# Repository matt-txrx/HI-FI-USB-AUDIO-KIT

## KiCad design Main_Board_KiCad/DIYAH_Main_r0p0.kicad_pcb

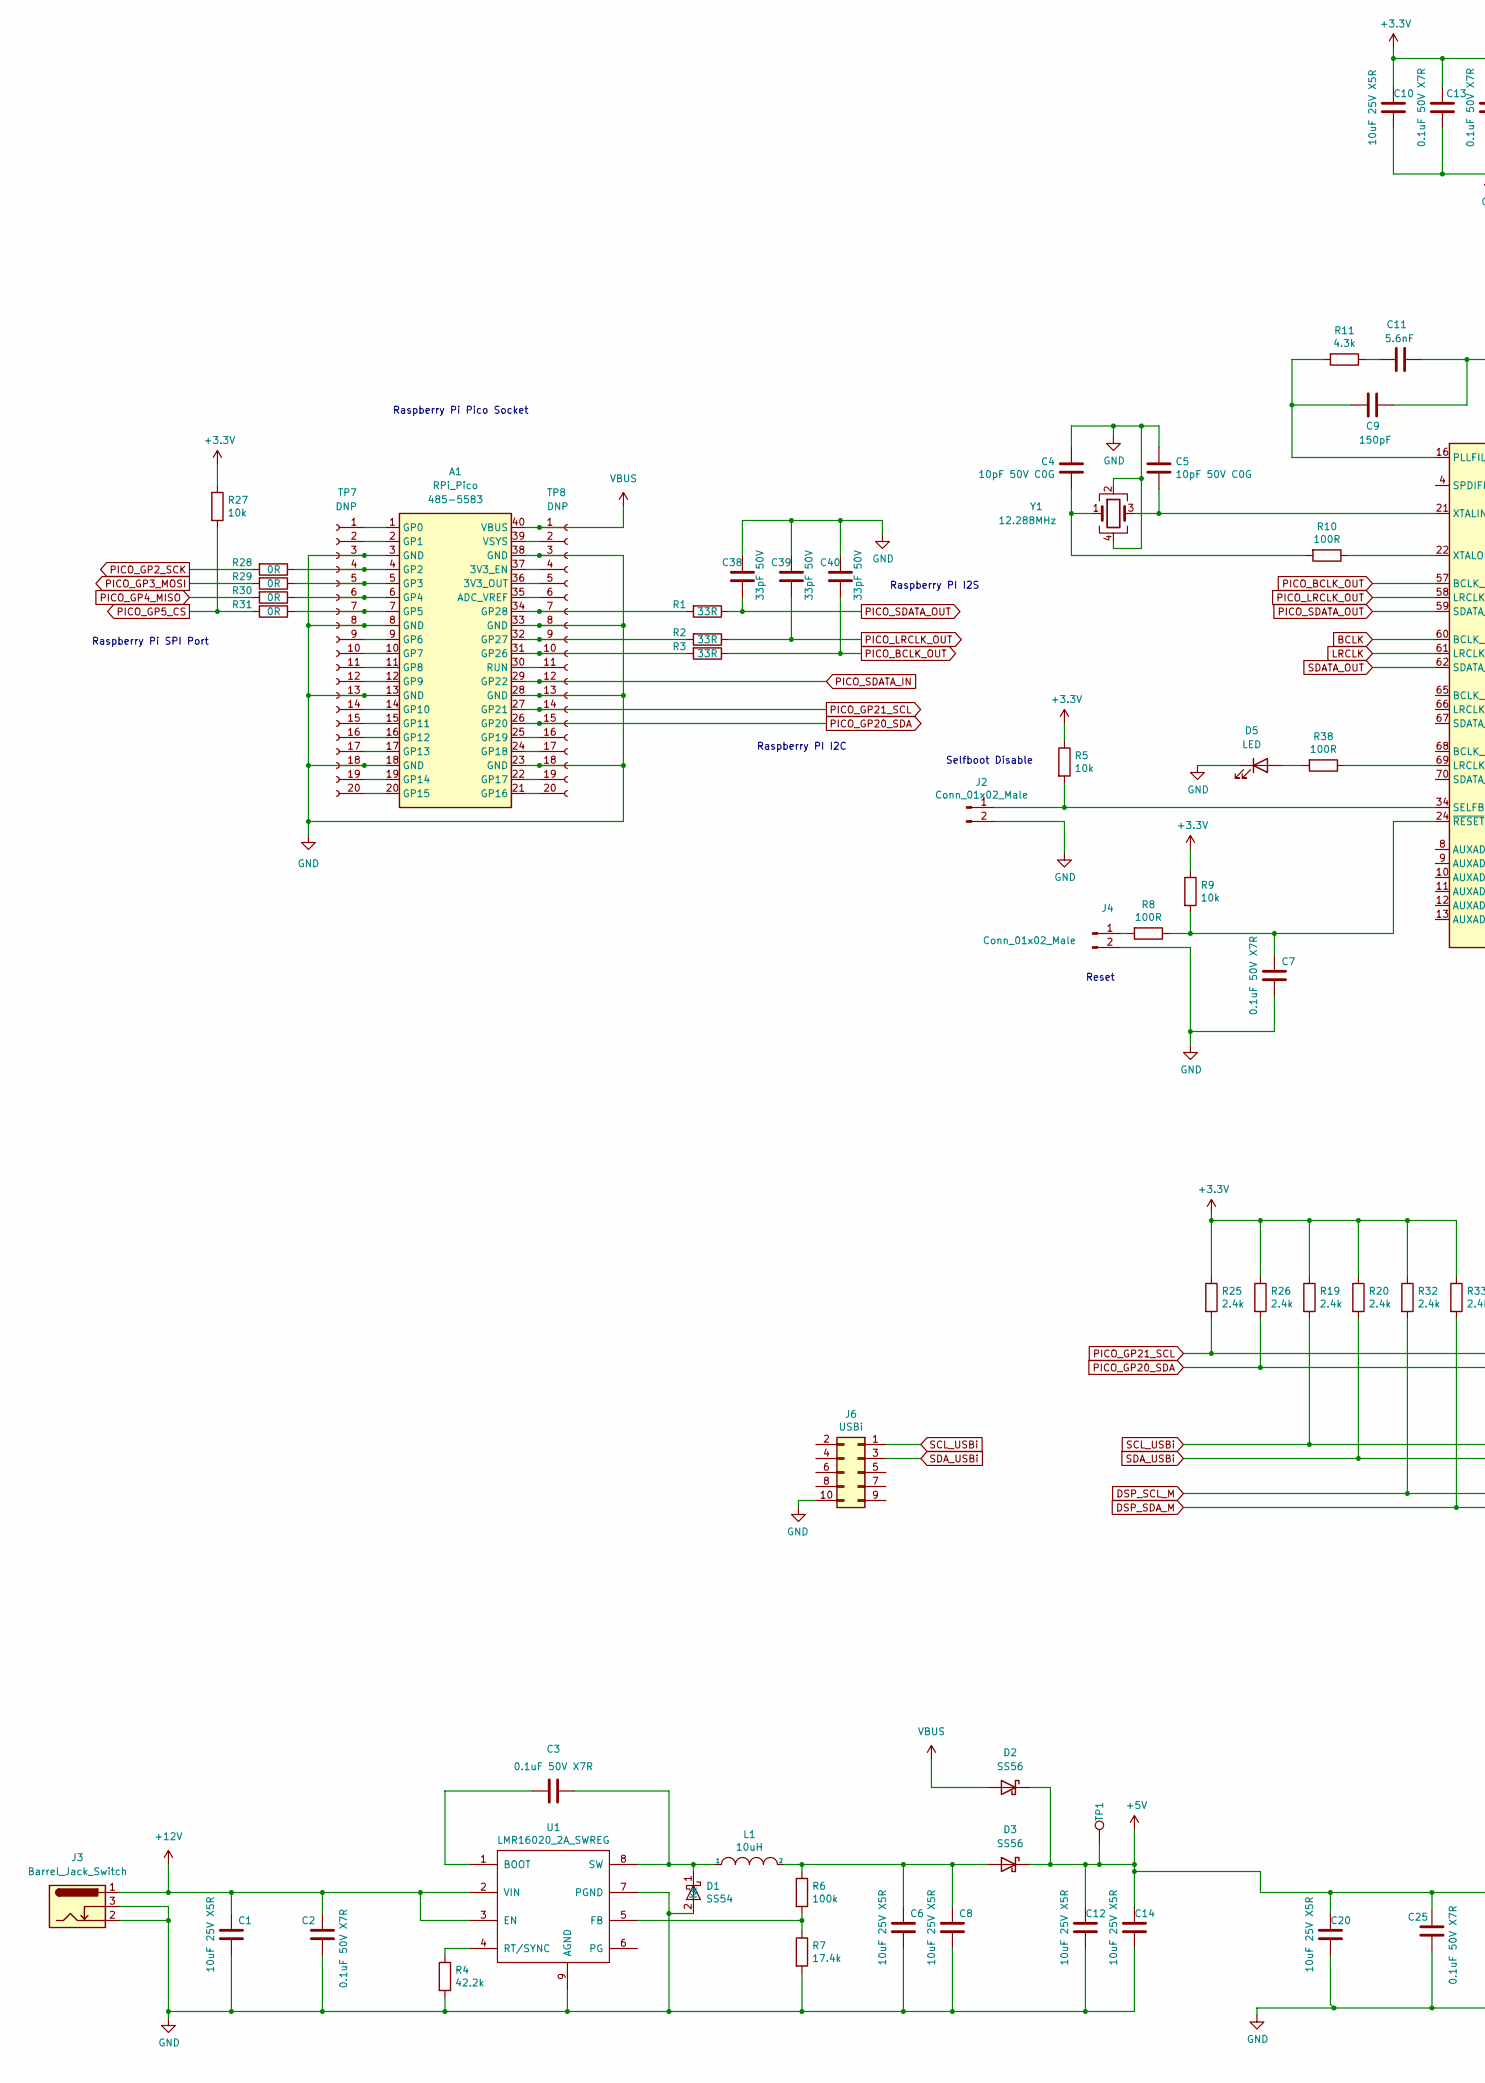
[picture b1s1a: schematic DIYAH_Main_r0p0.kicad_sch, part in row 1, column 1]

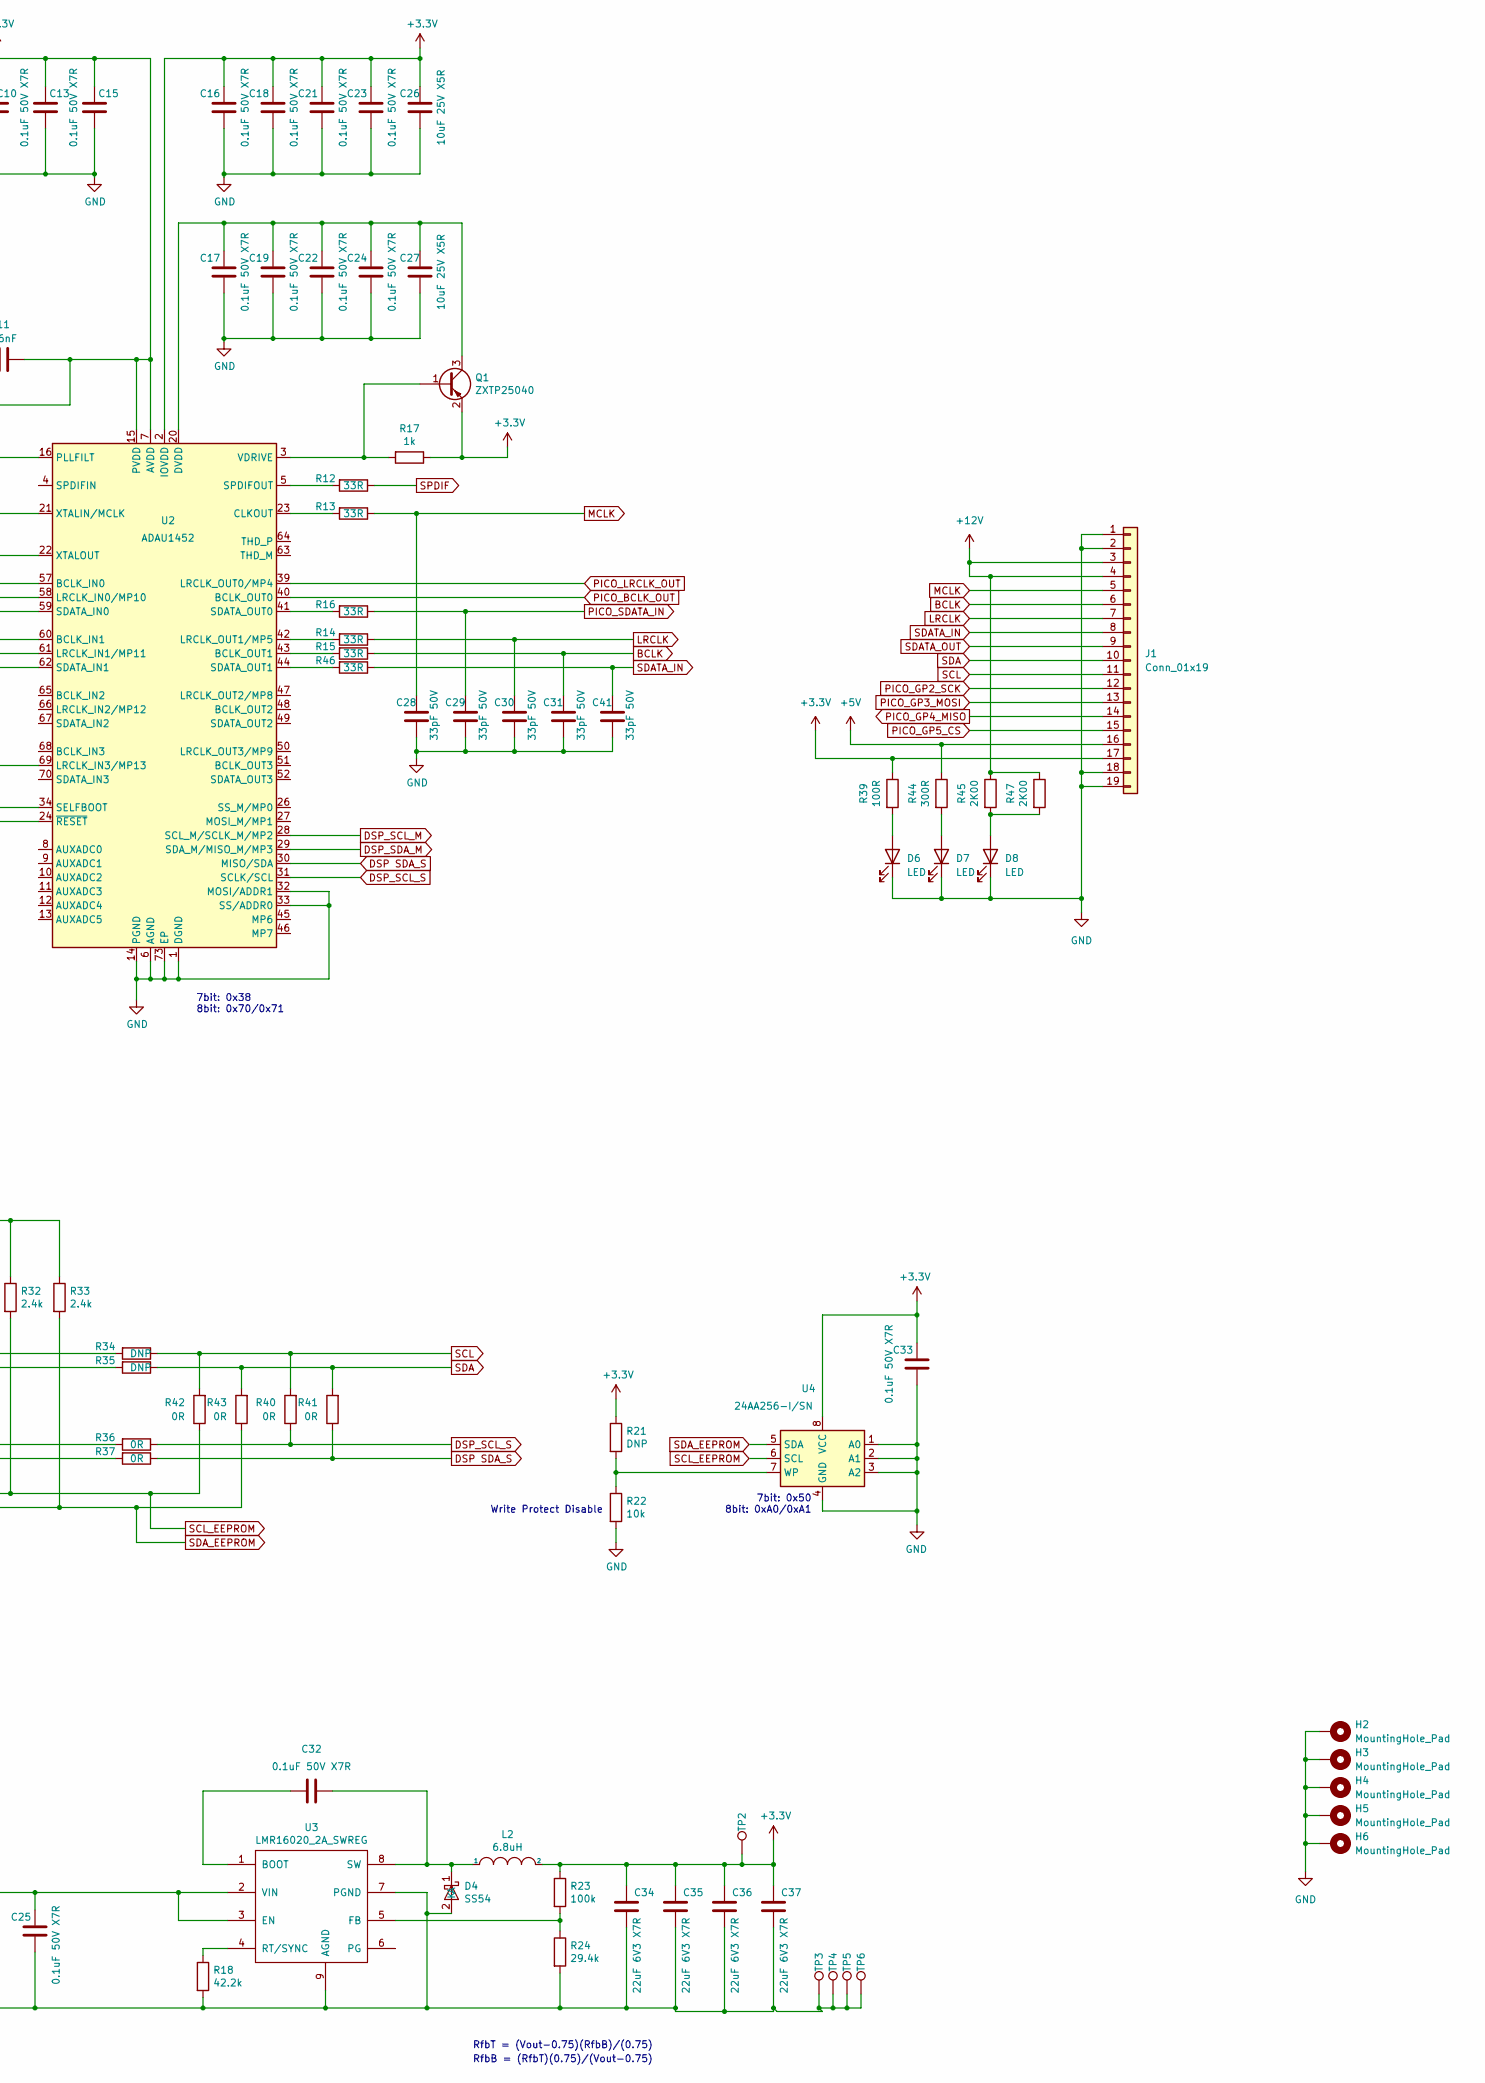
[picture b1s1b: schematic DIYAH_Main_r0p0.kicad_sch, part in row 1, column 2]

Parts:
A1: RPi_Pico; Rpi_Pico; Mouser 485-5583
C1, C6, C8, C10, C12, C14, C20, C26, C27: 10uF 25V X5R; C_0805_2012Metric_Pad1.18x1.45mm_HandSolder; Part Number CL21A106KAYNNNE; LCSC Part # C15850
C2, C3, C7, C13, C15, C16, C17, C18, C19, C21, C22, C23, C24, C25, C32, C33: 0.1uF 50V X7R; C_0603_1608Metric_Pad1.08x0.95mm_HandSolder; Part Number CC0603KRX7R9BB104; LCSC Part # C14663
C4, C5: 10pF 50V C0G; C_0603_1608Metric_Pad1.08x0.95mm_HandSolder; Part Number CL10C100JB8NNNC; LCSC Part # C1634
C9: 150pF; C_0603_1608Metric_Pad1.08x0.95mm_HandSolder; Part Number CL10B151KB8NNNC; LCSC Part # C170148
C11: 5.6nF; C_0603_1608Metric_Pad1.08x0.95mm_HandSolder; Part Number CL10B562KB8NNNC; LCSC Part # C170143
C28, C29, C30, C31, C38, C39, C40, C41: 33pF 50V; C_0603_1608Metric_Pad1.08x0.95mm_HandSolder; Part Number CL10C330JB8NNNC; LCSC Part # C1663
C34, C35, C36, C37: 22uF 6V3 X7R; C_0805_2012Metric_Pad1.18x1.45mm_HandSolder; Part Number CL21A226MAQNNNE; LCSC Part # C45783
D1, D4: SS54; D_SMA; Part Number SS54-HF; Mouser 750-SS54-HF
D2, D3: SS56; D_SMB; LCSC Part # C2897835
D5, D6, D7, D8: LED; LED_1206_3216Metric_Pad1.42x1.75mm_HandSolder; LCSC Part # C434442
H2, H3, H4, H5, H6: MountingHole_Pad; MountingHole_3.2mm_M3_Pad_Via
J1: Conn_01x19; PinSocket_1x19_P2.54mm_Vertical
J2, J4: Conn_01x02_Male; PinHeader_1x02_P2.54mm_Vertical
J3: Barrel_Jack_Switch; BarrelJack_GCT_DCJ200-10-A_Horizontal; Mouser 640-DCJ200-10-A-K1-K
J6: USBi; IDC-Header_2x05_P2.54mm_Vertical
L1: 10uH; Coilcraft_XAL40xx; Part Number XAL4040-103MEC; Mouser 994-XAL4040-103MEC
L2: 6.8uH; L_7.3x7.3_H3.5; Part Number 0618CDMCCDS-6R8MC; Mouser 851-0618CDMCCDS6R8MC
Q1: ZXTP25040; SOT-23; Part Number ZXTP25040DFHTA; Mouser 621-ZXTP25040DFHTA
R1, R2, R3, R12, R13, R14, R15, R16, R46: 33R; R_0603_1608Metric_Pad0.98x0.95mm_HandSolder; Part Number 0603WAF330JT5E; LCSC Part # C23140
R4, R18: 42.2k; R_0603_1608Metric_Pad0.98x0.95mm_HandSolder; Part Number 0603WAF4422T5E; LCSC Part # C23056
R5, R9, R22, R27: 10k; R_0603_1608Metric_Pad0.98x0.95mm_HandSolder; Part Number 0603WAF1002T5E; LCSC Part # C25804
R6, R23: 100k; R_0603_1608Metric_Pad0.98x0.95mm_HandSolder; Part Number 0603WAF1003T5E; LCSC Part # C25803
R7: 17.4k; R_0603_1608Metric_Pad0.98x0.95mm_HandSolder; Part Number 0603WAF1742T5E; LCSC Part # C22819
R8, R10, R38, R39: 100R; R_0603_1608Metric_Pad0.98x0.95mm_HandSolder; Part Number 0603WAF1000T5E; LCSC Part # C22775
R11: 4.3k; R_0603_1608Metric_Pad0.98x0.95mm_HandSolder; Part Number 0603WAF4301T5E; LCSC Part # C23159
R17: 1k; R_0603_1608Metric_Pad0.98x0.95mm_HandSolder; Part Number 0603WAF1001T5E; LCSC Part # C25804
R19, R20, R25, R26, R32, R33: 2.4k; R_0603_1608Metric_Pad0.98x0.95mm_HandSolder; Part Number 0603WAF2401T5E; LCSC Part # C22940
R21, R34, R35: DNP; R_0603_1608Metric_Pad0.98x0.95mm_HandSolder
R24: 29.4k; R_0603_1608Metric_Pad0.98x0.95mm_HandSolder; Part Number 0603WAF2942T5E; LCSC Part # C22974
R28, R29, R30, R31, R36, R37, R40, R41, R42, R43: 0R; R_0603_1608Metric_Pad0.98x0.95mm_HandSolder; Part Number 0603WAF0000T5E; LCSC Part # C21189
R44: 300R; R_0603_1608Metric_Pad0.98x0.95mm_HandSolder; Part Number 0603WAF3000T5E; LCSC Part # C23025
R45, R47: 2K00; R_0603_1608Metric_Pad0.98x0.95mm_HandSolder; Part Number 0603WAF2001T5E; LCSC Part # C22975
TP1, TP2, TP3, TP4, TP5, TP6: DNP; TestPoint_Keystone_5000-5004_Miniature
TP7, TP8: DNP; PinHeader_1x20_P2.54mm_Vertical
U1, U3: LMR16020_2A_SWREG; HSOP-8-1EP_3.9x4.9mm_P1.27mm_EP2.41x3.1mm_ThermalVias; Part Number LMR16020PDDAR; LCSC Part # C190006
U2: ADAU1452; LFCSP-72-1EP_10x10mm_P0.5mm_EP5.3x5.3mm; Part Number ADAU1452WBCPZ; LCSC Part # C403699
U4: 24AA256-I/SN; SOIC-8_3.9x4.9mm_P1.27mm; Part Number 24AA256-I/SN; LCSC Part # C152169
Y1: 12.288MHz; Crystal_SMD_3225-4Pin_3.2x2.5mm_HandSoldering; Part Number SMD-3225_4P 12.288MHZ 12PF 10PPM -40~+8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; LCSC Part # C362472

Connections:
+3.3V: C9.1, C10.1, C11.2, C13.2, C15.2, C16.2, C18.2, C21.2, C23.2, C26.1, C33.2, C34.1, C35.1, C36.1, C37.1, J1.17, L2.2, Q1.2 (E), R5.1, R9.1, R17.1, R19.1, R20.1, R21.1, R23.1, R25.1, R26.1, R27.1, R32.1, R33.1, R39.1, TP2.1, U2.2 (IOVDD), U2.7 (AVDD), U2.15 (PVDD), U2.18 (IOVDD), U2.38 (IOVDD), U2.56 (IOVDD), U4.8 (VCC)
+5V: C12.1, C14.1, C20.1, C25.2, D2.1 (K), D3.1 (K), J1.16, R44.1, TP1.1, U3.2 (VIN), U3.3 (EN)
+12V: C1.1, C2.2, J1.3, J1.4, J3.1, R45.1, R47.1, U1.2 (VIN), U1.3 (EN)
BCLK: C31.1, J1.6, R15.1, U2.60 (BCLK_IN1)
DSP SDA_S: R37.1, R41.1, U2.30 (MISO/SDA)
DSP_SCL_M: R32.2, R42.1, U2.28 (SCL_M/SCLK_M/MP2), U4.6 (SCL)
DSP_SCL_S: R36.1, R40.1, U2.31 (SCLK/SCL)
DSP_SDA_M: R33.2, R43.1, U2.29 (SDA_M/MISO_M/MP3), U4.5 (SDA)
GND: A1.3 (GND), A1.8 (GND), A1.13 (GND), A1.18 (GND), A1.23 (GND), A1.28 (GND), A1.33 (GND), A1.38 (GND), C1.2, C2.1, C4.1, C5.1, C6.2, C7.1, C8.2, C10.2, C12.2, C13.1, C14.2, C15.1, C16.1, C17.1, C18.1, C19.1, C20.2, C21.1, C22.1, C23.1, C24.1, C25.1, C26.2, C27.2, C28.2, C29.2, C30.2, C31.2, C33.1, C34.2, C35.2, C36.2, C37.2, C38.1, C39.1, C40.1, C41.2, D1.2 (A), D4.2 (A), D5.1 (K), D6.1 (K), D7.1 (K), D8.1 (K), H2.1, H3.1, H4.1, H5.1, H6.1, J1.1, J1.2, J1.18, J1.19, J2.2, J3.2, J3.3, J4.2, J6.10, R4.2, R7.2, R18.2, R22.2, R24.2, TP3.1, TP4.1, TP5.1, TP6.1, TP7.3, TP7.8, TP7.13, TP7.18, TP8.3, TP8.8, TP8.13, TP8.18, U1.7 (PGND), U1.9 (AGND), U2.1 (DGND), U2.6 (AGND), U2.14 (PGND), U2.17 (DGND), U2.19 (DGND), U2.25 (DGND), U2.32 (MOSI/ADDR1), U2.33 (SS/ADDR0), U2.36 (DGND), U2.37 (DGND), U2.54 (DGND), U2.55 (DGND), U2.72 (DGND), U2.73 (EP), U3.7 (PGND), U3.9 (AGND), U4.1 (A0), U4.2 (A1), U4.3 (A2), U4.4 (GND), Y1.2, Y1.4
LRCLK: C30.1, J1.7, R14.1, U2.61 (LRCLK_IN1/MP11)
MCLK: C28.1, J1.5, R13.1
unnamed: A1.1 (GP0), TP7.1
unnamed: A1.2 (GP1), TP7.2
unnamed: A1.4 (GP2), R28.1, TP7.4
unnamed: A1.5 (GP3), R29.1, TP7.5
unnamed: A1.6 (GP4), R30.1, TP7.6
unnamed: A1.7 (GP5), R31.1, TP7.7
unnamed: A1.9 (GP6), TP7.9
unnamed: A1.10 (GP7), TP7.10
unnamed: A1.11 (GP8), TP7.11
unnamed: A1.12 (GP9), TP7.12
unnamed: A1.14 (GP10), TP7.14
unnamed: A1.15 (GP11), TP7.15
unnamed: A1.16 (GP12), TP7.16
unnamed: A1.17 (GP13), TP7.17
unnamed: A1.19 (GP14), TP7.19
unnamed: A1.20 (GP15), TP7.20
unnamed: A1.21 (GP16), TP8.20
unnamed: A1.22 (GP17), TP8.19
unnamed: A1.24 (GP18), TP8.17
unnamed: A1.25 (GP19), TP8.16
unnamed: A1.30 (RUN), TP8.11
unnamed: A1.31 (GP26), R3.2, TP8.10
unnamed: A1.32 (GP27), R2.2, TP8.9
unnamed: A1.34 (GP28), R1.2, TP8.7
unnamed: A1.35 (ADC_VREF), TP8.6
unnamed: A1.36 (3V3_OUT), TP8.5
unnamed: A1.37 (3V3_EN), TP8.4
unnamed: A1.39 (VSYS), TP8.2
unnamed: C3.1, D1.1 (K), L1.1, U1.8 (SW)
unnamed: C3.2, U1.1 (BOOT)
unnamed: C4.2, R10.2, Y1.1
unnamed: C5.2, U2.21 (XTALIN/MCLK), Y1.3
unnamed: C6.1, C8.1, D3.2 (A), L1.2, R6.1
unnamed: C7.2, R8.1, R9.2, U2.24 (~RESET)
unnamed: C9.2, R11.2, U2.16 (PLLFILT)
unnamed: C11.1, R11.1
unnamed: C17.2, C19.2, C22.2, C24.2, C27.1, Q1.3 (C), U2.20 (DVDD), U2.35 (DVDD), U2.53 (DVDD), U2.71 (DVDD)
unnamed: C32.1, D4.1 (K), L2.1, U3.8 (SW)
unnamed: C32.2, U3.1 (BOOT)
unnamed: D5.2 (A), R38.2
unnamed: D6.2 (A), R39.2
unnamed: D7.2 (A), R44.2
unnamed: D8.2 (A), R45.2, R47.2
unnamed: J2.1, R5.2, U2.34 (SELFBOOT)
unnamed: J4.1, R8.2
unnamed: Q1.1 (B), R17.2, U2.3 (VDRIVE)
unnamed: R4.1, U1.4 (RT/SYNC)
unnamed: R6.2, R7.1, U1.5 (FB)
unnamed: R10.1, U2.22 (XTALOUT)
unnamed: R12.2, U2.5 (SPDIFOUT)
unnamed: R13.2, U2.23 (CLKOUT)
unnamed: R14.2, U2.42 (LRCLK_OUT1/MP5)
unnamed: R15.2, U2.43 (BCLK_OUT1)
unnamed: R16.2, U2.41 (SDATA_OUT0)
unnamed: R18.1, U3.4 (RT/SYNC)
unnamed: R21.2, R22.1, U4.7 (WP)
unnamed: R23.2, R24.1, U3.5 (FB)
unnamed: R38.1, U2.69 (LRCLK_IN3/MP13)
unnamed: R46.2, U2.44 (SDATA_OUT1)
PICO_BCLK_OUT: C40.2, R3.1, U2.40 (BCLK_OUT0), U2.57 (BCLK_IN0)
PICO_GP2_SCK: J1.12, R28.2
PICO_GP3_MOSI: J1.13, R29.2
PICO_GP4_MISO: J1.14, R30.2
PICO_GP5_CS: J1.15, R27.2, R31.2
PICO_GP20_SDA: A1.26 (GP20), R26.2, R35.2, TP8.15
PICO_GP21_SCL: A1.27 (GP21), R25.2, R34.2, TP8.14
PICO_LRCLK_OUT: C39.2, R2.1, U2.39 (LRCLK_OUT0/MP4), U2.58 (LRCLK_IN0/MP10)
PICO_SDATA_IN: A1.29 (GP22), C29.1, R16.1, TP8.12
PICO_SDATA_OUT: C38.2, R1.1, U2.59 (SDATA_IN0)
SCL: J1.11, R34.1, R40.2, R42.2
SCL_USBi: J6.1, R19.2, R36.2
SDA: J1.10, R35.1, R41.2, R43.2
SDATA_IN: C41.1, J1.8, R46.1
SDATA_OUT: J1.9, U2.62 (SDATA_IN1)
SDA_USBi: J6.3, R20.2, R37.2
SPDIF: R12.1
VBUS: A1.40 (VBUS), D2.2 (A), TP8.1

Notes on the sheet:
RfbB = (RfbT)(0.75)/(Vout-0.75)
Raspberry PI I2C
Raspberry Pi SPI Port
RfbT = (Vout-0.75)(RfbB)/(0.75)
7bit: 0x38 8bit: 0x70/0x71
Selfboot Disable
Write Protect Disable
7bit: 0x50 8bit: 0xA0/0xA1
Reset
Raspberry PI I2S
Raspberry Pi Pico Socket

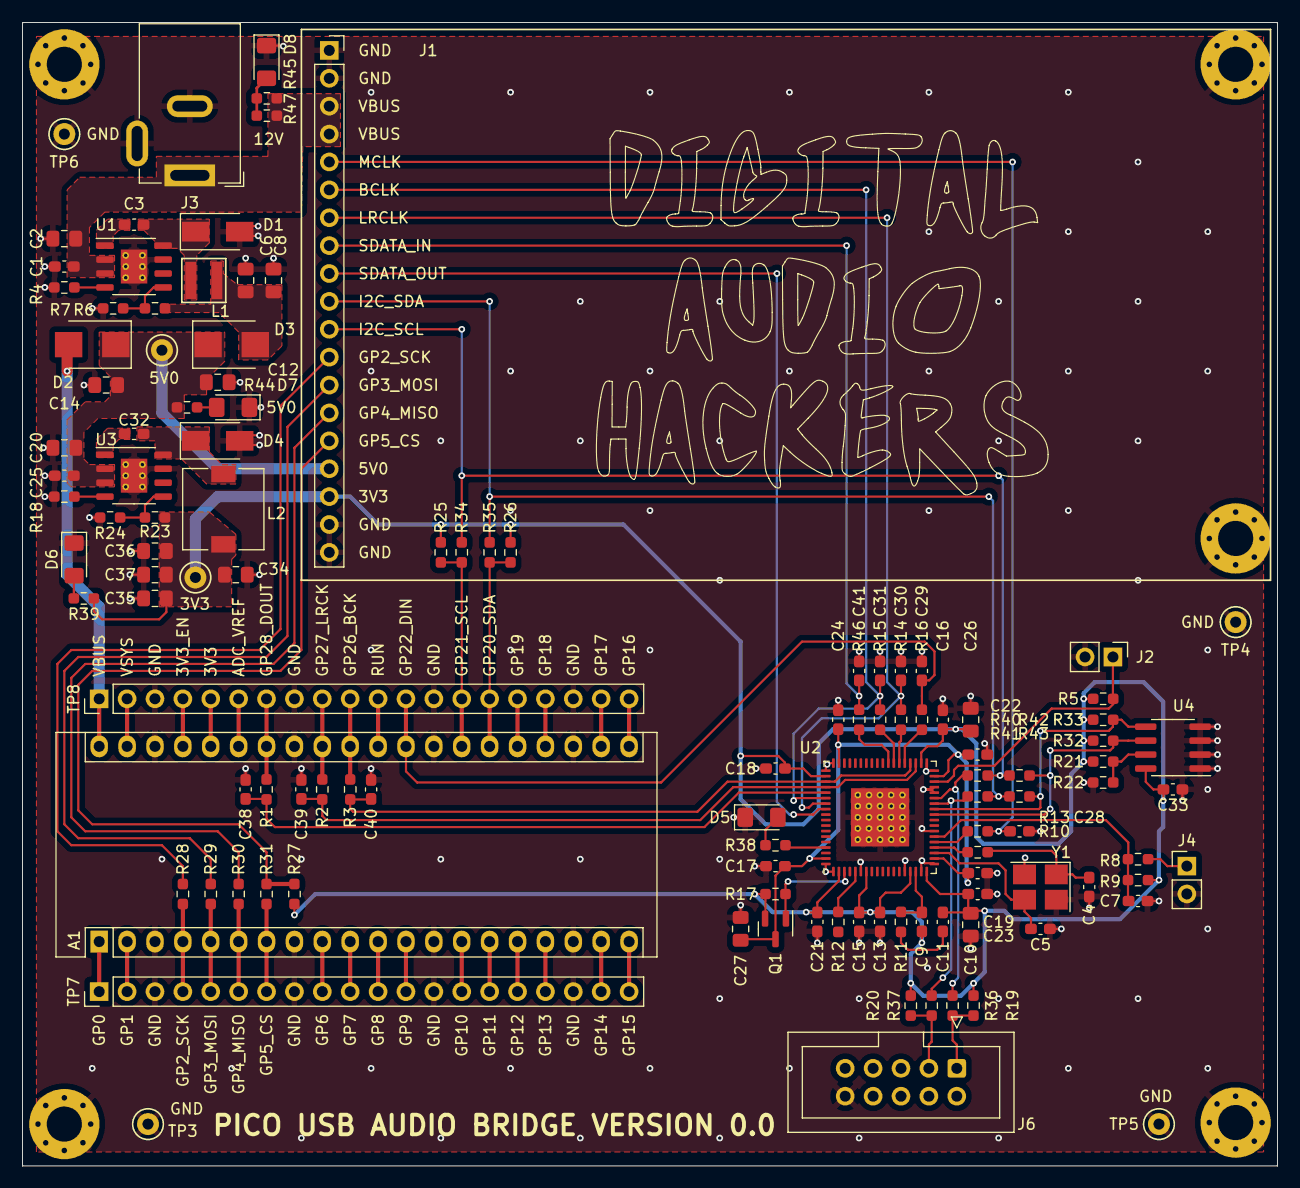
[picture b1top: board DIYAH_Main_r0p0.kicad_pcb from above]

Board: 2 copper layers, 114.3 x 104.1 mm, 123 parts (0 on the bottom side), 87 nets.

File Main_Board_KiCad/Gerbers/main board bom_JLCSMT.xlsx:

Comment | Designator | Footprint | JLCPCB Part #（optional）
RPi_Pico | A1
10uF 25V X5R | C1, C6, C8, C10, C12, C14, C20, C26, C27 |  | C15850
0.1uF 50V X7R | C2, C3, C7, C13, C15, C16, C17, C18, C19, C21, C22, C23, C24, C25, C32, C33 |  | C14663
10pF 50V C0G | C4, C5 |  | C1634
150pF | C9 |  | C170148
5.6nF | C11 |  | C170143
33pF 50V | C28, C29, C30, C31, C38, C39, C40, C41 |  | C1663
22uF 6V3 X7R | C34, C35, C36, C37 |  | C45783
SS54 | D1, D4 |  | C3014014
SS56 | D2, D3 |  | C2897835
LED | D5, D6, D7, D8 |  | C434442
MountingHole_Pad | H2, H3, H4, H5, H6
Conn_01x19 | J1
Conn_01x02_Male | J2, J4
Barrel_Jack_Switch | J3
USBi | J6
10uH | L1 |  | C5144883
6.8uH | L2 |  | C2638689
ZXTP25040 | Q1 |  | C211430
33R | R1, R2, R3, R12, R13, R14, R15, R16, R46 |  | C23140
42.2k | R4, R18 |  | C23056
10k | R5, R9, R22, R27 |  | C25804
100k | R6, R23 |  | C25803
17.4k | R7 |  | C22819
100R | R8, R10, R38, R39 |  | C22775
4.3k | R11 |  | C23159
1k | R17 |  | C25804
2.4k | R19, R20, R25, R26, R32, R33 |  | C22940
DNP | R21, R34, R35
29.4k | R24 |  | C22974
0R | R28, R29, R30, R31, R36, R37, R40, R41, R42, R43 |  | C21189
300R | R44 |  | C23025
2K00 | R45, R47 |  | C22975
DNP | TP1, TP2, TP3, TP4, TP5, TP6
LMR16020_2A_SWREG | U1, U3 |  | C190006
ADAU1452 | U2 |  | C403699
24AA256-I/SN | U4 |  | C152169
12.288MHz | Y1 |  | C362472

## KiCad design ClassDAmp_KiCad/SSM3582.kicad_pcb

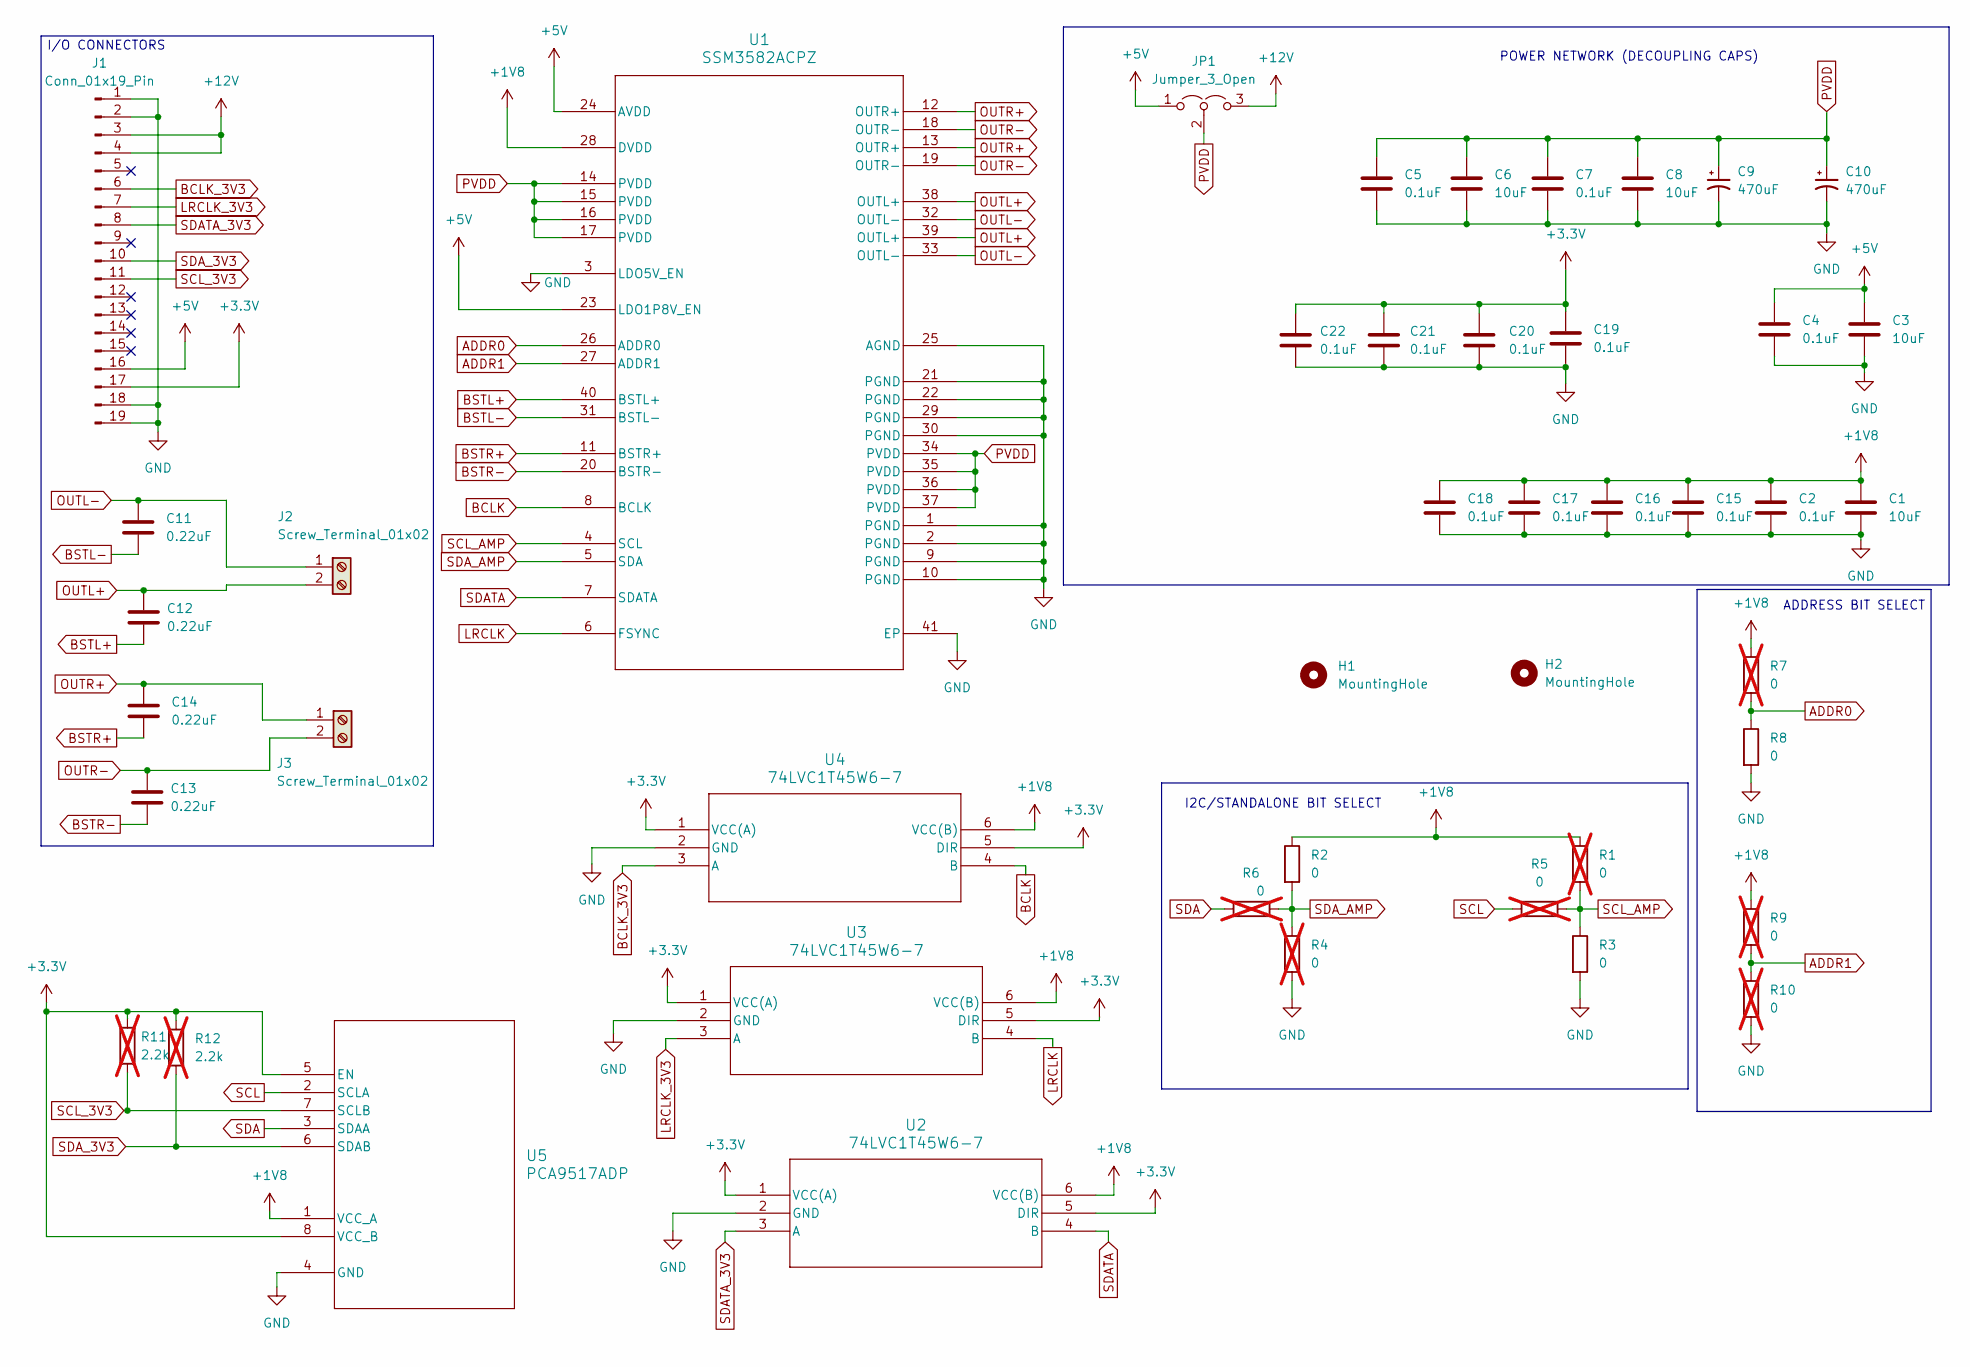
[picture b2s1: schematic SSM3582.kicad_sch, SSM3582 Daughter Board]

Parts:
C1, C3, C6, C8: 10uF; C_0805_2012Metric; LCSC C1713
C2, C4, C5, C7, C15, C16, C17, C18, C19, C20, C21, C22: 0.1uF; C_0603_1608Metric; LCSC C1591
C9, C10: 470uF; CP_Elec_6.3x7.7; LCSC C5354997
C11, C12, C13, C14: 0.22uF; C_0603_1608Metric; LCSC C21120
H1, H2: MountingHole; MountingHole_3.2mm_M3
J1: Conn_01x19_Pin; PinHeader_1x19_P2.54mm_Vertical
J2, J3: Screw_Terminal_01x02; TerminalBlock_Phoenix_MKDS-1,5-2-5.08_1x02_P5.08mm_Horizont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; LCSC C89120
JP1: Jumper_3_Open; PinHeader_1x03_P2.54mm_Vertical
R1, R4, R5, R6, R7, R9, R10: 0; R_1812_4532Metric; not fitted
R2, R3, R8: 0; R_1812_4532Metric; LCSC C270976
R11, R12: 2.2k; R_1812_4532Metric; not fitted
U1: SSM3582ACPZ; CP_40_7_ADI; LCSC C4991352
U2, U3, U4: 74LVC1T45W6-7; SOT-23-6; LCSC C168856
U5: PCA9517ADP; SOT505-1_NXP; LCSC C80799

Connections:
+1V8: C1.1, C2.1, C15.1, C16.1, C17.1, C18.1, R1.1, R2.1, R7.1, R9.1, U1.28 (DVDD), U2.6 (VCC(B)), U3.6 (VCC(B)), U4.6 (VCC(B)), U5.1 (VCC_A)
+3.3V: C19.1, C20.1, C21.1, C22.1, J1.17, R11.1, R12.1, U2.1 (VCC(A)), U2.5 (DIR), U3.1 (VCC(A)), U3.5 (DIR), U4.1 (VCC(A)), U4.5 (DIR), U5.5 (EN), U5.8 (VCC_B)
+5V: C3.1, C4.1, J1.16, JP1.1 (A), U1.23 (LDO1P8V_EN), U1.24 (AVDD)
+12V: J1.3, J1.4, JP1.3 (B)
ADDR0: R7.2, R8.1, U1.26 (ADDR0)
ADDR1: R9.2, R10.1, U1.27 (ADDR1)
BCLK: U1.8 (BCLK), U4.4 (B)
BCLK_3V3: J1.6, U4.3 (A)
BSTL+: C12.2, U1.40 (BSTL+)
BSTL-: C11.2, U1.31 (BSTL-)
BSTR+: C14.2, U1.11 (BSTR+)
BSTR-: C13.2, U1.20 (BSTR-)
GND: C1.2, C2.2, C3.2, C4.2, C5.2, C6.2, C7.2, C8.2, C9.2, C10.2, C15.2, C16.2, C17.2, C18.2, C19.2, C20.2, C21.2, C22.2, J1.1, J1.2, J1.18, J1.19, R3.2, R4.2, R8.2, R10.2, U1.1 (PGND), U1.2 (PGND), U1.3 (LDO5V_EN), U1.9 (PGND), U1.10 (PGND), U1.21 (PGND), U1.22 (PGND), U1.25 (AGND), U1.29 (PGND), U1.30 (PGND), U1.41 (EP), U2.2 (GND), U3.2 (GND), U4.2 (GND), U5.4 (GND)
LRCLK: U1.6 (FSYNC), U3.4 (B)
LRCLK_3V3: J1.7, U3.3 (A)
OUTL+: C12.1, J2.2, U1.38 (OUTL+), U1.39 (OUTL+)
OUTL-: C11.1, J2.1, U1.32 (OUTL-), U1.33 (OUTL-)
OUTR+: C14.1, J3.1, U1.12 (OUTR+), U1.13 (OUTR+)
OUTR-: C13.1, J3.2, U1.18 (OUTR-), U1.19 (OUTR-)
PVDD: C5.1, C6.1, C7.1, C8.1, C9.1, C10.1, JP1.2 (C), U1.14 (PVDD), U1.15 (PVDD), U1.16 (PVDD), U1.17 (PVDD), U1.34 (PVDD), U1.35 (PVDD), U1.36 (PVDD), U1.37 (PVDD)
SCL: R5.1, U5.2 (SCLA)
SCL_3V3: J1.11, R11.2, U5.7 (SCLB)
SCL_AMP: R1.2, R3.1, R5.2, U1.4 (SCL)
SDA: R6.1, U5.3 (SDAA)
SDATA: U1.7 (SDATA), U2.4 (B)
SDATA_3V3: J1.8, U2.3 (A)
SDA_3V3: J1.10, R12.2, U5.6 (SDAB)
SDA_AMP: R2.2, R4.1, R6.2, U1.5 (SDA)

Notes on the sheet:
I2C/STANDALONE BIT SELECT
POWER NETWORK (DECOUPLING CAPS)
ADDRESS BIT SELECT
I/O CONNECTORS

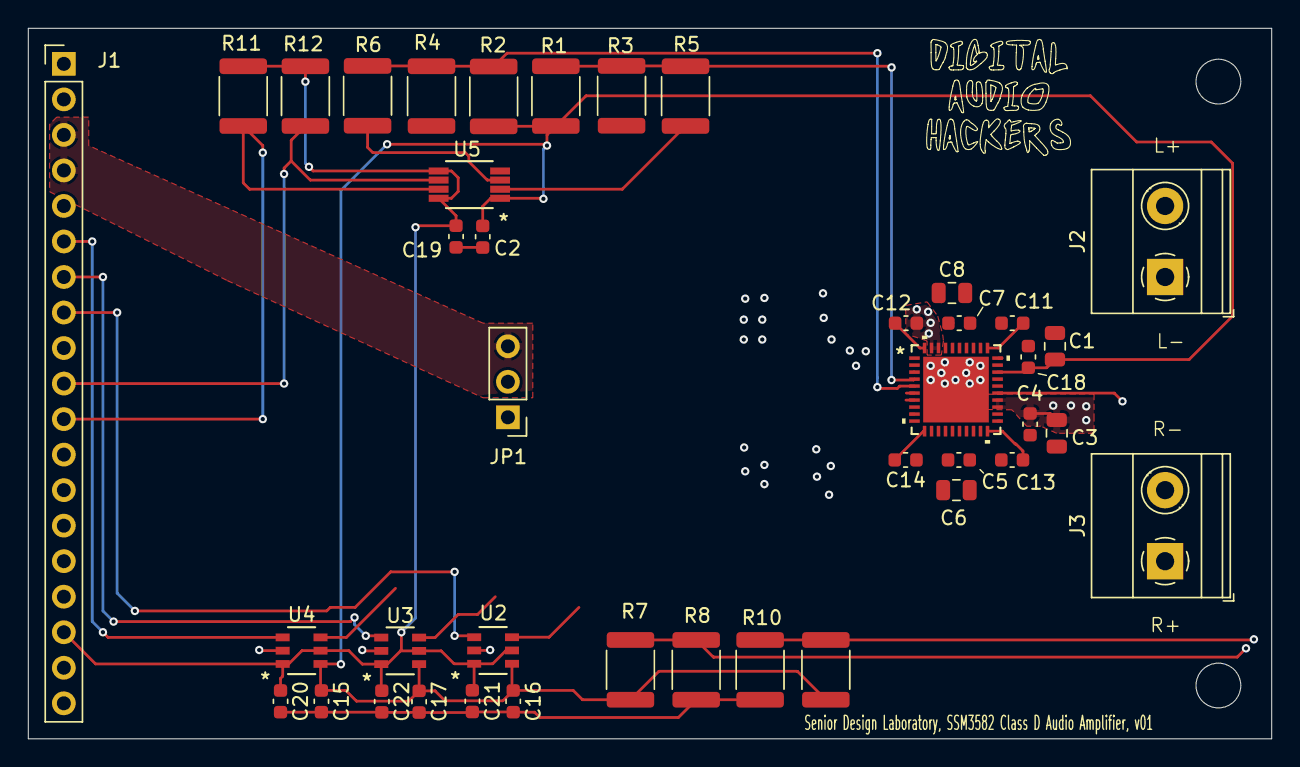
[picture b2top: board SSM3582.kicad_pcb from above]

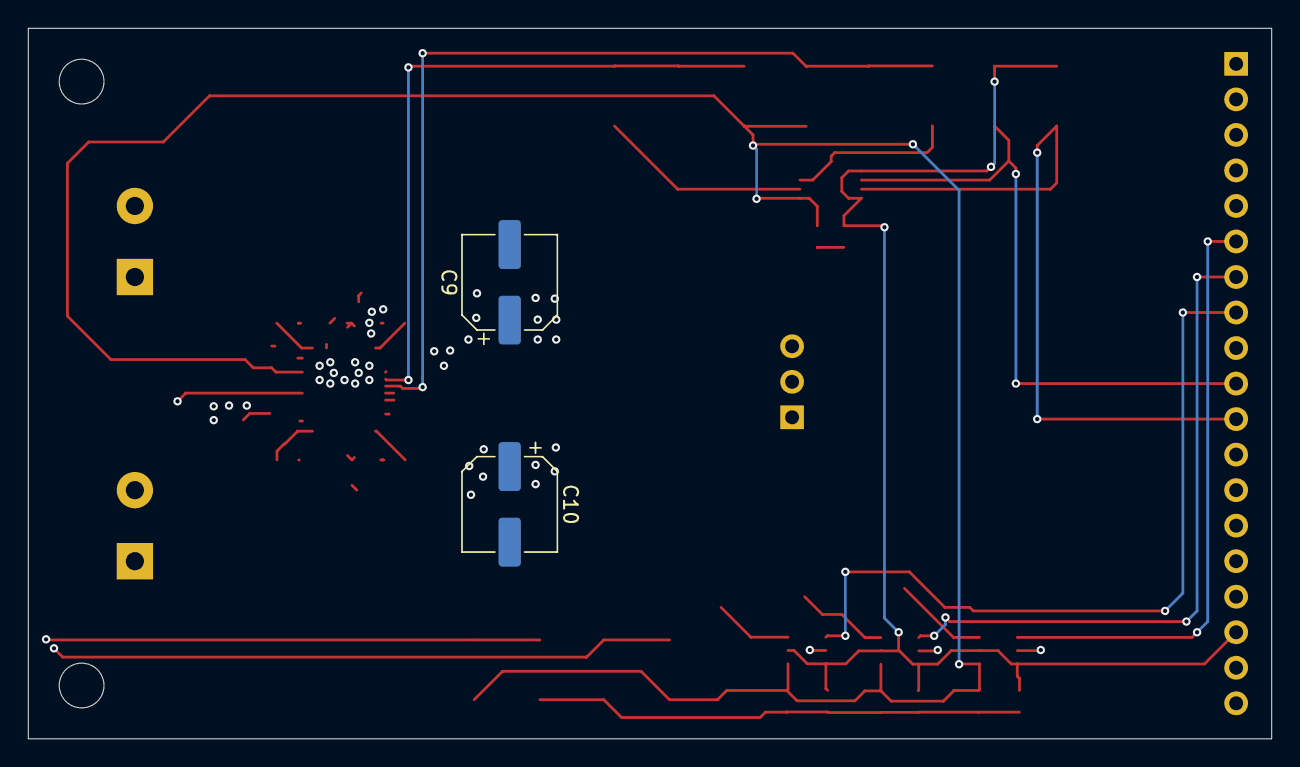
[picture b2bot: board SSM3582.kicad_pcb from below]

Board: 2 copper layers, 88.9 x 50.8 mm, 45 parts (2 on the bottom side), 28 nets.

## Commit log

2024-04-20 Create 3D_Printed_Case
